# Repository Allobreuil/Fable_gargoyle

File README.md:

# 🗿 Fable Gargoyle

Interactive recreation of the **gargoyles from Fable II**.  
This project combines **electronics**, **embedded software (Arduino Nano ESP32)**, and **3D modeling** to bring a talking, reactive gargoyle to life.

---

## 📂 Project structure

- **3d_model/** → 3D models of the gargoyle (3D printing)  
- **hardware/** → electronic schematics and PCB (KiCad)  
- **software/** → source code for Arduino Nano ESP32  
- **sounds_fr/** → French audio files for the gargoyle voice  

---

## 🛠️ Required hardware

- [Arduino Nano ESP32](https://store.arduino.cc/products/nano-esp32)  
- [Speaker](https://www.amazon.fr/XYWHPGV-Haut-parleur-Diam%C3%A8tre-projet-%C3%A9lectronique/dp/B0CP25TYPF)  
- [DFPlayer Mini MP3 Player](https://www.amazon.fr/dp/B089D5NLW1?ref=ppx_yo2ov_dt_b_fed_asin_title)  
- [Switch](https://www.amazon.fr/Interrupteur-Commutateur-Conviennent-%C3%89lectroniques-dInterrupteur/dp/B086QGZRKG)  
- [9V Battery](https://www.amazon.fr/Duracell-Piles-9V-Plus-paquet/dp/B093LQHR2Y)  
- [5V Regulator L7805CV](https://www.amazon.fr/STMICROELECTRONICS-r%C3%A9gulateurs-tension-positive-L7805CV/dp/B007DQ4FXC)  
- [9V Battery power cable](https://www.amazon.fr/dp/B076NQXMP2?ref=ppx_yo2ov_dt_b_fed_asin_title)  
- [SD card](https://www.amazon.fr/dp/B08GY9NYRM?ref=ppx_yo2ov_dt_b_fed_asin_title)  
- [HC-SR501 Motion Sensor](https://www.amazon.fr/dp/B071FBG4XW?ref=ppx_yo2ov_dt_b_fed_asin_title)  

## ⚡ Installation

### 1. Electronics
- Open the `hardware/` folder in **KiCad** to check the schematic and PCB.  
- Assemble and solder the listed components.  
- Connect the speaker and the motion sensor according to the schematic.  

### 2. Software
1. Install the Arduino IDE and ESP32 drivers.  
2. Add ESP32 board support in the Arduino IDE.  
3. Open the `software/` folder.  
4. Flash the code named **`Gargoyle_V2`** to the Arduino Nano ESP32.  

### 3. 3D Model
- The files in the `3d_model/` folder can be used to 3D print the gargoyle.  
- The folder also includes a **split version of the gargoyle**, divided into several parts to make large-scale printing easier.  
- You can adjust the model to your needs (size, material, color).  

---

## 📖 User Manual

1. **Prepare the SD card**  
   - Copy all the `.mp3` files from the `sounds_fr/` folder.  
   - Paste them onto a FAT32-formatted SD card.  
   - Insert the SD card into the MP3 module.  

2. **Flash the Arduino**  
   - Open `Gargoyle_V2` in the `software/` folder with the Arduino IDE.  
   - Select the **Arduino Nano ESP32** board in the IDE.  
   - Flash the program to the microcontroller.  

3. **Assemble the system**  
   - Solder the components according to the KiCad schematic (`hardware/`).  
   - Insert the Arduino into the circuit.  
   - Connect the speaker, motion sensor, switch, and regulator.  
   - Power the system with a 9V battery.  

4. **Usage**  
   - Once powered on, the system is ready.  
   - When the **HC-SR501 motion sensor** detects movement in front of the gargoyle,  
     the Arduino plays a **random sound** from the SD card through the speaker.  

---

## 🤝 Contribution

Contributions are welcome:  
- Adding new voices or translations  
- Improving the ESP32 code (optimizations, new sensors, etc.)  
- Enhancing the 3D model (mechanical or aesthetic improvements)  

---

## 📜 License

- The **source code** (`software/` folder) is released under the **MIT License**.  
- The **hardware schematics** (`hardware/` folder) are also shared under the **MIT License**.  

⚠️ **Important**:  
- The **3D model** and **audio files** are **fan-made recreations** inspired by *Fable II*.  
- These elements are **copyrighted by their respective owners (Microsoft)**.  
- They are provided here **for educational and non-commercial purposes only**.  
- No copyright infringement is intended.  

---

## ⚖️ Legal Notice

This is a **fan project** inspired by *Fable II*.  
- The gargoyle model and sounds remain the intellectual property of Microsoft.  
- This repository is shared **for personal, educational, and non-commercial use only**.  
- Redistribution or commercial use of the copyrighted material is not permitted.  

---

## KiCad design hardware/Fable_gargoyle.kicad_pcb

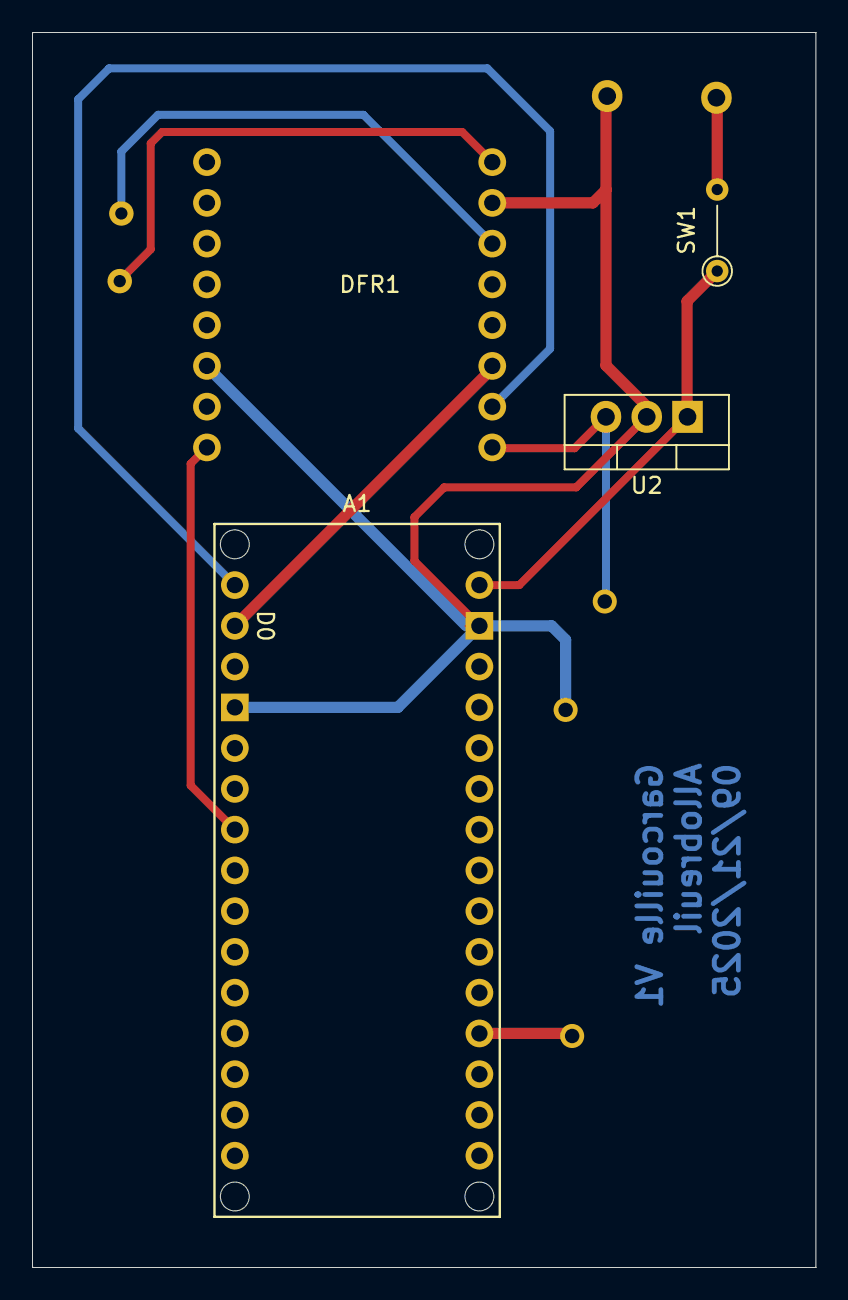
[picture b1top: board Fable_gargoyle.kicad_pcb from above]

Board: 2 copper layers, 48.8 x 77.0 mm, 4 parts (0 on the bottom side), 6 nets.

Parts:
A1: Arduino_Nano_ESP32_Socket
DFR1: DFPlayer
SW1: SW_Nidec_CAS-120A1; R_Axial_DIN0204_L3.6mm_D1.6mm_P5.08mm_Vertical
U2: LM7805_TO220; TO-220-3_Vertical

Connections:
GND: A1.GND1 (GND), A1.GND2 (GND), DFR1.7 (GND), U2.2 (GND)
unnamed: A1.D0 (D0/RX), DFR1.3 (TX)
unnamed: A1.D1 (D1/TX), DFR1.2 (RX)
unnamed: A1.D4, DFR1.16 (BUSY)
unnamed: DFR1.1 (VCC), U2.3 (VO)
unnamed: A1.VIN, SW1.1 (C), U2.1 (VI)
